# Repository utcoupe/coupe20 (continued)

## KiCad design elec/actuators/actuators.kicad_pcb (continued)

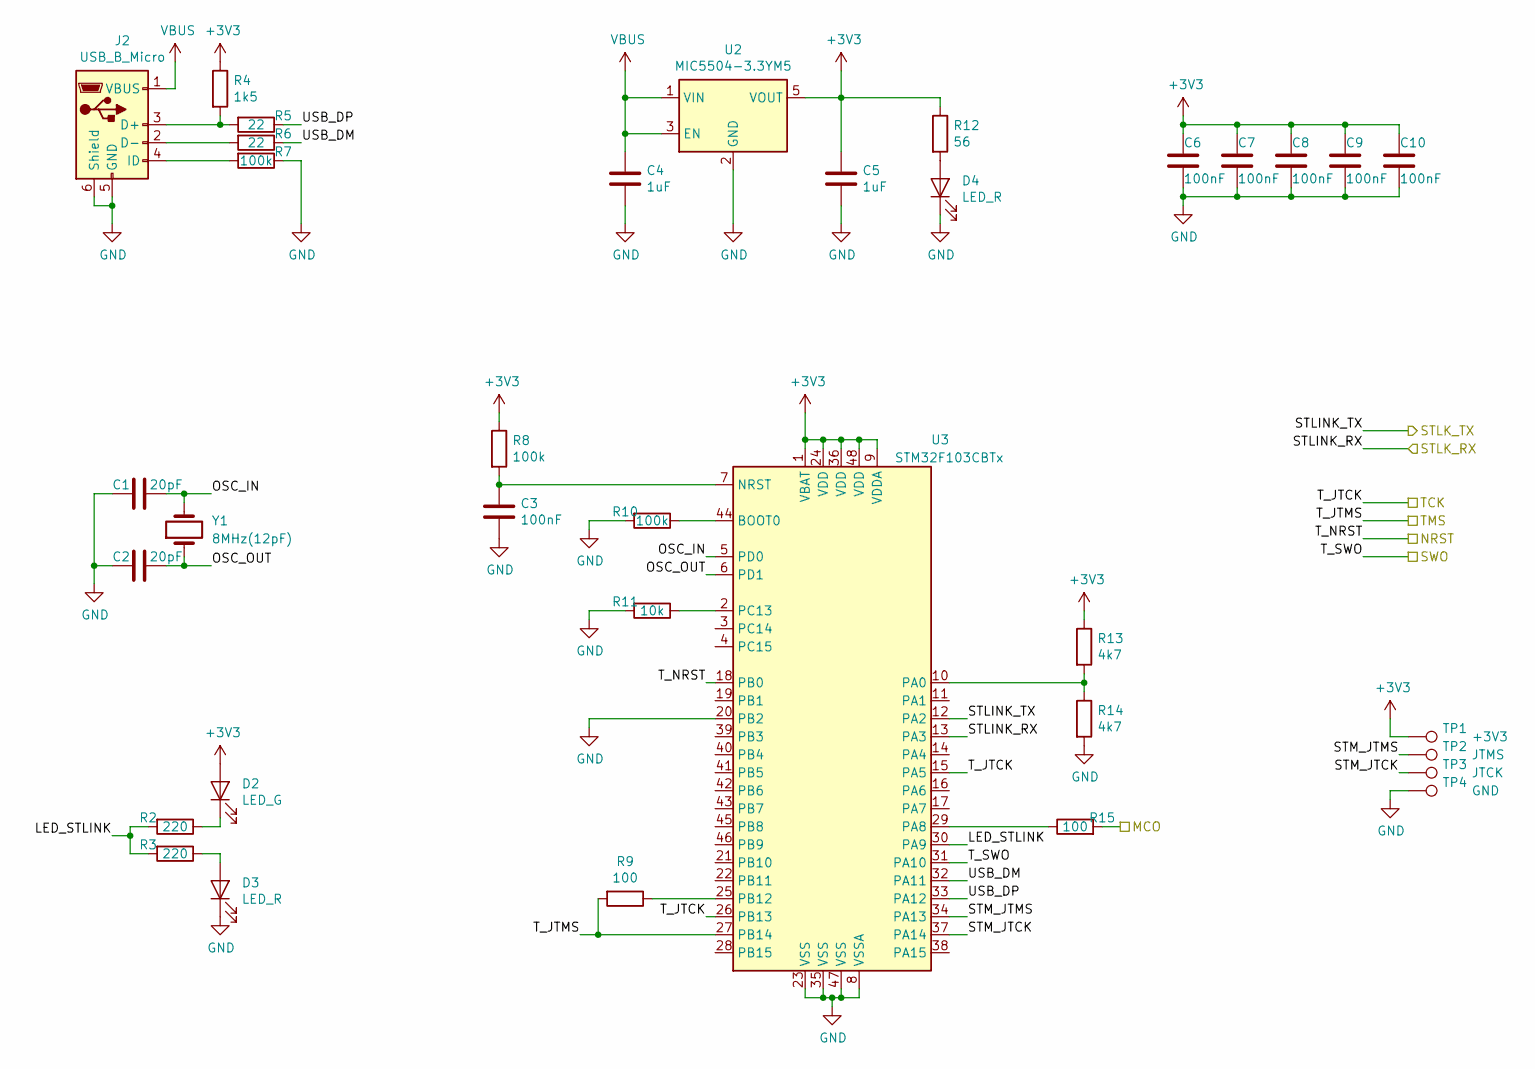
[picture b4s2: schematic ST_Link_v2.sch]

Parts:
C1, C2: 20pF; C_0805_2012Metric
C3, C6, C7, C8, C9, C10: 100nF; C_0805_2012Metric
C4, C5: 1uF; C_0805_2012Metric
D2: LED_G; LED_0805_2012Metric
D3, D4: LED_R; LED_0805_2012Metric
J2: USB_B_Micro; USB_Micro-B_Molex_47346-0001
R2, R3: 220; R_0805_2012Metric
R4: 1k5; R_0805_2012Metric
R5, R6: 22; R_0805_2012Metric
R7, R8, R10: 100k; R_0805_2012Metric
R9, R15: 100; R_0805_2012Metric
R11: 10k; R_0805_2012Metric
R12: 56; R_0805_2012Metric
R13, R14: 4k7; R_0805_2012Metric
TP1: +3V3; TestPoint_Pad_1.0x1.0mm
TP2: JTMS; TestPoint_Pad_1.0x1.0mm
TP3: JTCK; TestPoint_Pad_1.0x1.0mm
TP4: GND; TestPoint_Pad_1.0x1.0mm
U2: MIC5504-3.3YM5; SOT-23-5
U3: STM32F103CBTx; LQFP-48_7x7mm_P0.5mm
Y1: 8MHz(12pF); Crystal_SMD_HC49-SD

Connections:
+3V3: C5.1, C6.1, C7.1, C8.1, C9.1, C10.1, D2.2 (A), R4.1, R8.1, R12.1, R13.1, TP1.1, U2.5 (VOUT), U3.1 (VBAT), U3.9 (VDDA), U3.24 (VDD), U3.36 (VDD), U3.48 (VDD); also elsewhere on the board
/STM32F446RE6/MCO: R15.2; also elsewhere on the board
/STM32F446RE6/NRST: U3.18 (PB0); also elsewhere on the board
/STM32F446RE6/SWO: U3.31 (PA10); also elsewhere on the board
/STM32F446RE6/TCK: U3.15 (PA5), U3.26 (PB13); also elsewhere on the board
/STM32F446RE6/TMS: R9.2, U3.27 (PB14); also elsewhere on the board
/ST_Link_v2/LED_STLINK: R2.2, R3.2, U3.30 (PA9)
/ST_Link_v2/OSC_IN: C1.1, U3.5 (PD0), Y1.2
/ST_Link_v2/OSC_OUT: C2.2, U3.6 (PD1), Y1.1
/ST_Link_v2/STLK_RX: U3.13 (PA3); also elsewhere on the board
/ST_Link_v2/STLK_TX: U3.12 (PA2); also elsewhere on the board
/ST_Link_v2/STM_JTCK: TP3.1, U3.37 (PA14); also elsewhere on the board
/ST_Link_v2/STM_JTMS: TP2.1, U3.34 (PA13); also elsewhere on the board
/ST_Link_v2/USB_DM: R6.1, U3.32 (PA11)
/ST_Link_v2/USB_DP: R5.1, U3.33 (PA12)
unnamed: C3.1, R8.2, U3.7 (NRST)
unnamed: D2.1 (K), R2.1
unnamed: D3.2 (A), R3.1
unnamed: D4.2 (A), R12.2
unnamed: J2.2 (D-), R6.2
unnamed: J2.3 (D+), R4.2, R5.2
unnamed: J2.4 (ID), R7.2
unnamed: R9.1, U3.25 (PB12)
unnamed: R10.1, U3.44 (BOOT0)
unnamed: R11.1, U3.2 (PC13)
unnamed: R13.2, R14.1, U3.10 (PA0)
unnamed: R15.1, U3.29 (PA8)
VBUS: C4.1, J2.1 (VBUS), U2.1 (VIN), U2.3 (EN)

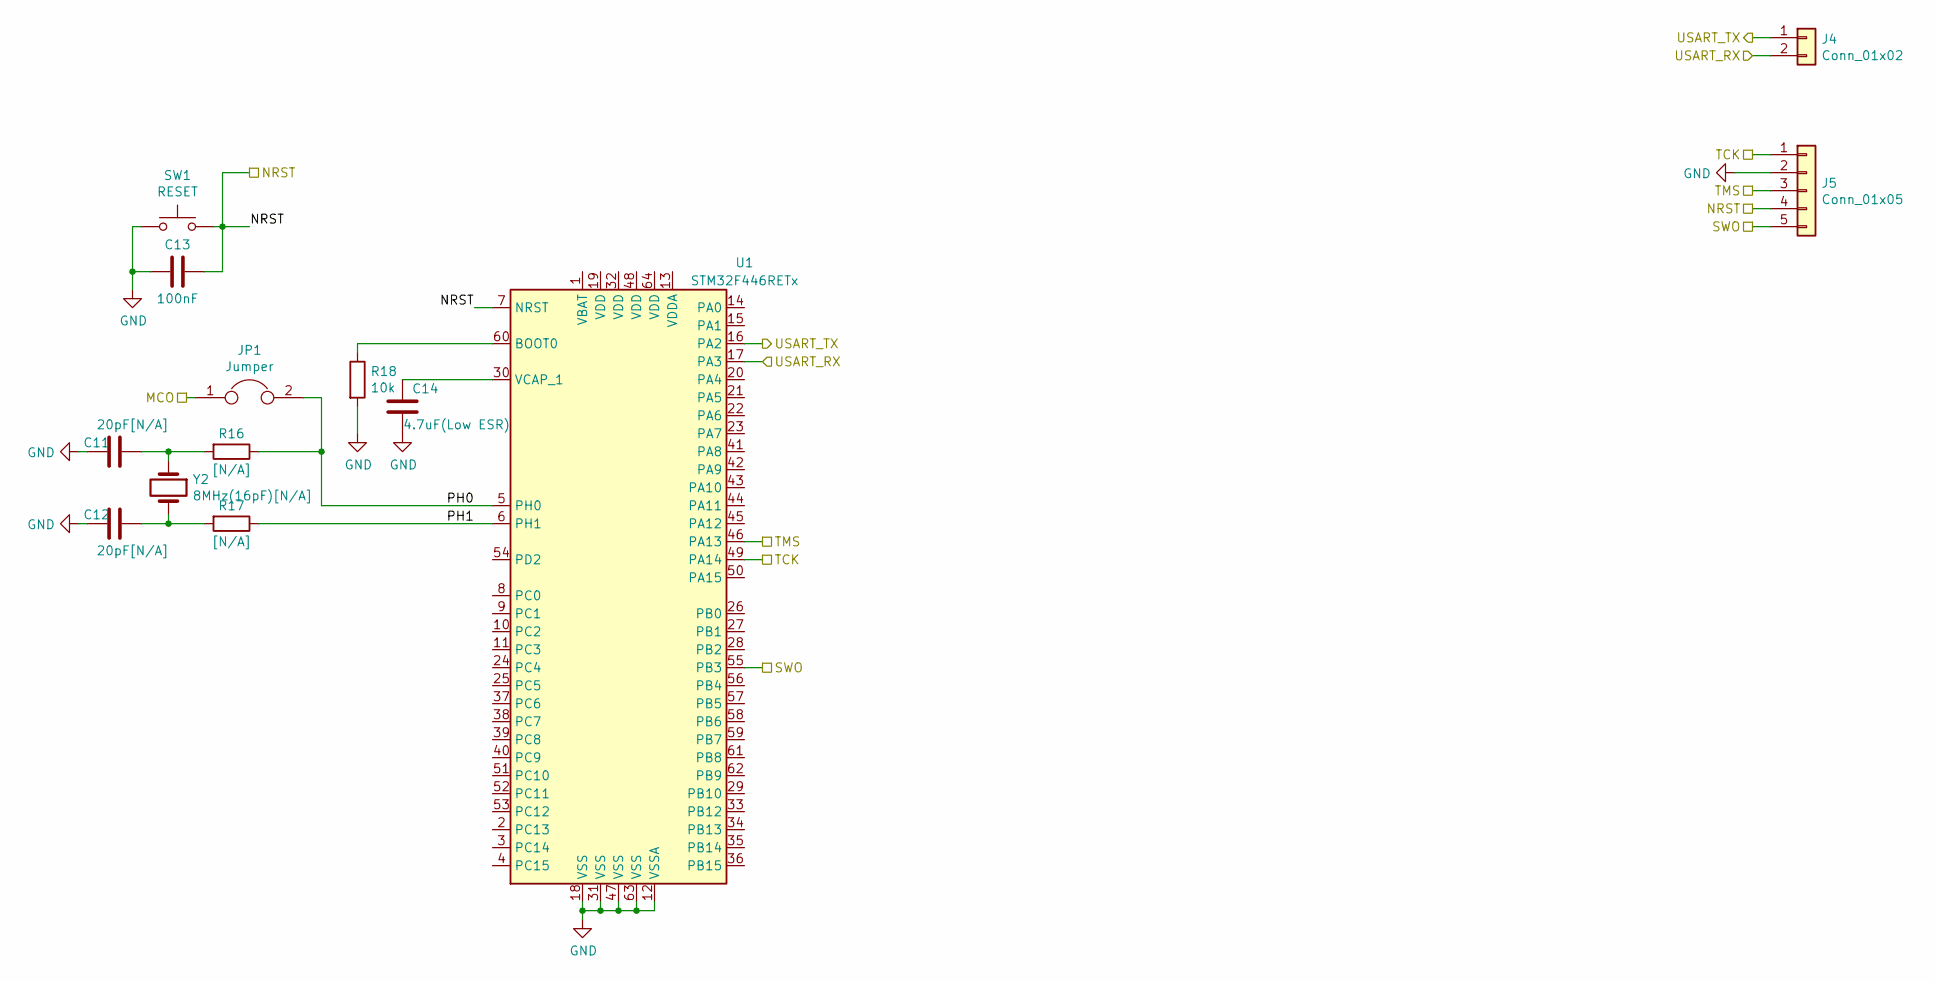
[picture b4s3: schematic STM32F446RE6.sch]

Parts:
C11, C12: 20pF[N/A]; C_0805_2012Metric
C13: 100nF; C_0805_2012Metric
C14: 4.7uF(Low ESR); C_0805_2012Metric
J4: Conn_01x02; PinHeader_1x02_P2.54mm_Vertical
J5: Conn_01x05; PinHeader_1x05_P2.54mm_Vertical
JP1: Jumper; SolderJumper-2_P1.3mm_Open_TrianglePad1.0x1.5mm
R16, R17: [N/A]; R_0805_2012Metric
R18: 10k; R_0805_2012Metric
SW1: RESET; SW_Push_1P1T_NO_CK_KSC6xxJ
U1: STM32F446RETx; LQFP-64_10x10mm_P0.5mm
Y2: 8MHz(16pF)[N/A]; Crystal_SMD_HC49-SD

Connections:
/STM32F446RE6/MCO: JP1.1; also elsewhere on the board
/STM32F446RE6/NRST: C13.1, J5.4, SW1.2, U1.7 (NRST); also elsewhere on the board
/STM32F446RE6/PH0: JP1.2, R16.1, U1.5 (PH0)
/STM32F446RE6/PH1: R17.1, U1.6 (PH1)
/STM32F446RE6/SWO: J5.5, U1.55 (PB3); also elsewhere on the board
/STM32F446RE6/TCK: J5.1, U1.49 (PA14); also elsewhere on the board
/STM32F446RE6/TMS: J5.3, U1.46 (PA13); also elsewhere on the board
/ST_Link_v2/STLK_RX: J4.1, U1.16 (PA2); also elsewhere on the board
/ST_Link_v2/STLK_TX: J4.2, U1.17 (PA3); also elsewhere on the board
unnamed: C11.1, R16.2, Y2.1
unnamed: C12.1, R17.2, Y2.2
unnamed: C14.1, U1.30 (VCAP_1)
unnamed: R18.1, U1.60 (BOOT0)

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
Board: 2 copper layers, 52 parts (0 on the bottom side), 37 nets, no tracks yet.

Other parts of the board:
J3: Conn_01x04; PinHeader_1x04_P2.54mm_Vertical

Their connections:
+3V3: J3.1; also elsewhere on the board
/ST_Link_v2/STM_JTCK: J3.3; also elsewhere on the board
/ST_Link_v2/STM_JTMS: J3.2; also elsewhere on the board

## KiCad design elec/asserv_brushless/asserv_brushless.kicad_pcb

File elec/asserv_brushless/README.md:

# Brushless PCB

[Interactive BOM](http://htmlpreview.github.io/?https://github.com/utcoupe/coupe20/blob/elec/elec/asserv_brushless/bom/ibom.html)

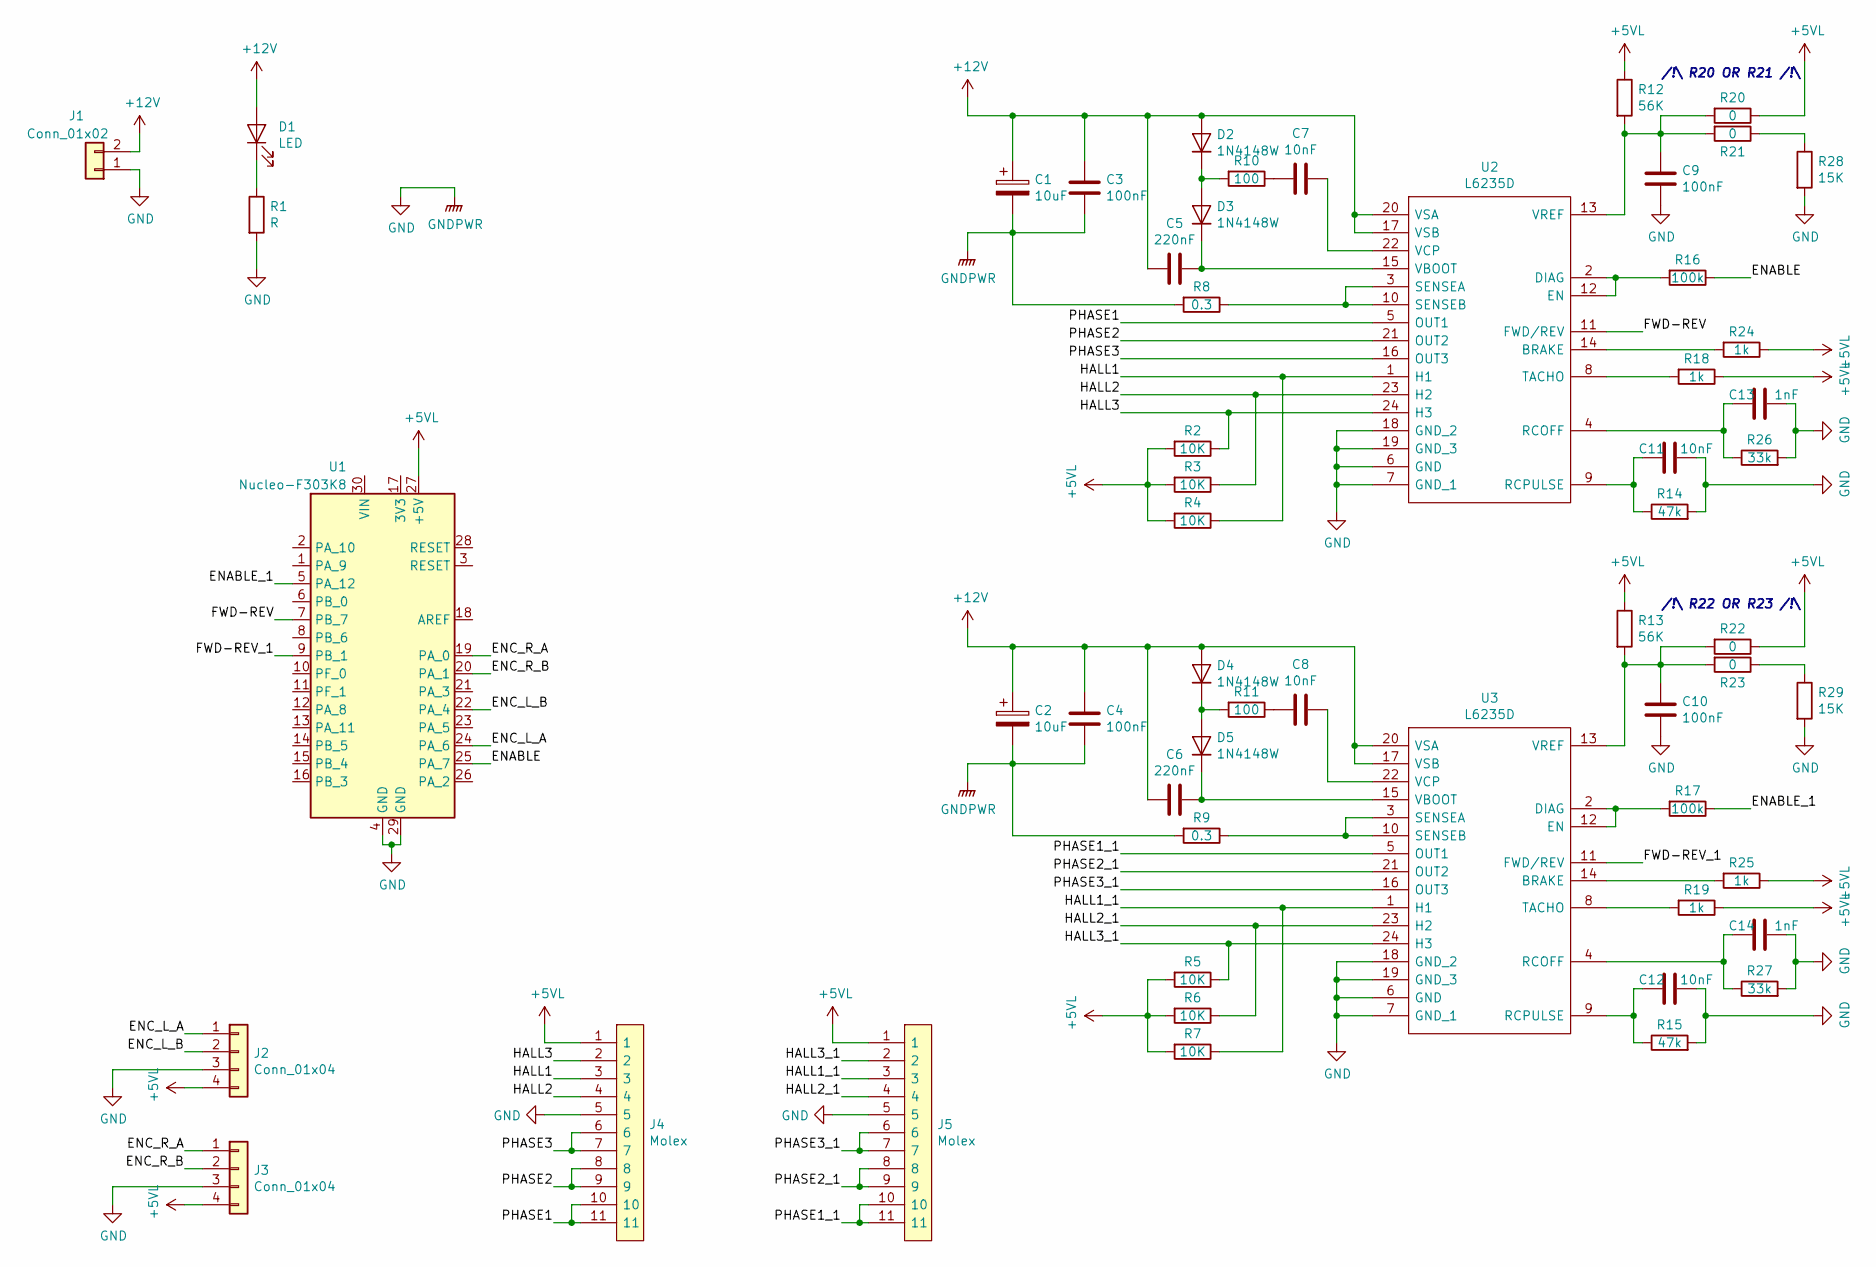
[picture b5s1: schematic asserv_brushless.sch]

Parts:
C1, C2: 10uF; CP_Elec_4x5.3
C3, C4, C9, C10: 100nF; C_0805_2012Metric
C5, C6: 220nF; C_0805_2012Metric
C7, C8, C11, C12: 10nF; C_0805_2012Metric
C13, C14: 1nF; C_0805_2012Metric
D1: LED; LED_0805_2012Metric
D2, D3, D4, D5: 1N4148W; D_SOD-123
J1: Conn_01x02; PhoenixContact_MSTBA_2,5_2-G-5,08_1x02_P5.08mm_Horizontal
J2, J3: Conn_01x04; Headers-Wire_Housings_HEADER_4POS_HE14
J4, J5: Molex; Molex_01x11_1mm_pitch_FFC-FPC; Manufacturer_Part_Number 52271-1179; Mouser Part Number 538-52271-1179
R1: R; R_0805_2012Metric
R2, R3, R4, R5, R6, R7: 10K; R_0805_2012Metric
R8, R9: 0.3; R_0805_2012Metric
R10, R11: 100; R_0805_2012Metric
R12, R13: 56K; R_0805_2012Metric
R14, R15: 47k; R_0805_2012Metric
R16, R17: 100k; R_0805_2012Metric
R18, R19, R24, R25: 1k; R_0805_2012Metric
R20, R21, R22, R23: 0; R_0805_2012Metric
R26, R27: 33k; R_0805_2012Metric
R28, R29: 15K; R_0805_2012Metric
U1: Nucleo-F303K8; NUCLEO-F303K8
U2, U3: L6235D; Manufacturer_Part_Number L6235D; Mouser Part Number 511-L6235D

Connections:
+5VL: J2.4, J3.4, J4.1, J5.1, R2.2, R3.2, R4.2, R5.2, R6.2, R7.2, R12.1, R13.1, R18.1, R19.1, R20.1, R22.1, R24.1, R25.1, U1.27 (+5V)
+12V: C1.1, C2.1, C3.1, C4.1, C5.2, C6.2, D1.2 (A), D2.2 (A), D4.2 (A), J1.2, U2.17 (VSB), U2.20 (VSA), U3.17 (VSB), U3.20 (VSA)
/ENABLE: R16.1, U1.25 (PA_7)
/ENABLE_1: R17.1, U1.5 (PA_12)
/ENC_L_A: J2.1, U1.24 (PA_6)
/ENC_L_B: J2.2, U1.22 (PA_4)
/ENC_R_A: J3.1, U1.19 (PA_0)
/ENC_R_B: J3.2, U1.20 (PA_1)
/FWD-REV: U1.7 (PB_7), U2.11 (FWD/REV)
/FWD-REV_1: U1.9 (PB_1), U3.11 (FWD/REV)
/HALL1: J4.3, R4.1, U2.1 (H1)
/HALL1_1: J5.3, R7.1, U3.1 (H1)
/HALL2: J4.4, R3.1, U2.23 (H2)
/HALL2_1: J5.4, R6.1, U3.23 (H2)
/HALL3: J4.2, R2.1, U2.24 (H3)
/HALL3_1: J5.2, R5.1, U3.24 (H3)
/PHASE1: J4.10, J4.11, U2.5 (OUT1)
/PHASE1_1: J5.10, J5.11, U3.5 (OUT1)
/PHASE2: J4.8, J4.9, U2.21 (OUT2)
/PHASE2_1: J5.8, J5.9, U3.21 (OUT2)
/PHASE3: J4.6, J4.7, U2.16 (OUT3)
/PHASE3_1: J5.6, J5.7, U3.16 (OUT3)
GND: C1.2, C2.2, C3.2, C4.2, C9.2, C10.2, C11.1, C12.1, C13.1, C14.1, J1.1, J2.3, J3.3, J4.5, J5.5, R1.2, R8.2, R9.2, R14.2, R15.2, R26.2, R27.2, R28.2, R29.2, U1.4 (GND), U1.29 (GND), U2.6 (GND), U2.7 (GND_1), U2.18 (GND_2), U2.19 (GND_3), U3.6 (GND), U3.7 (GND_1), U3.18 (GND_2), U3.19 (GND_3)
unnamed: C5.1, D3.1 (K), U2.15 (VBOOT)
unnamed: C6.1, D5.1 (K), U3.15 (VBOOT)
unnamed: C7.1, U2.22 (VCP)
unnamed: C7.2, R10.1
unnamed: C8.1, U3.22 (VCP)
unnamed: C8.2, R11.1
unnamed: C9.1, R12.2, R20.2, R21.2, U2.13 (VREF)
unnamed: C10.1, R13.2, R22.2, R23.2, U3.13 (VREF)
unnamed: C11.2, R14.1, U2.9 (RCPULSE)
unnamed: C12.2, R15.1, U3.9 (RCPULSE)
unnamed: C13.2, R26.1, U2.4 (RCOFF)
unnamed: C14.2, R27.1, U3.4 (RCOFF)
unnamed: D1.1 (K), R1.1
unnamed: D2.1 (K), D3.2 (A), R10.2
unnamed: D4.1 (K), D5.2 (A), R11.2
unnamed: R8.1, U2.3 (SENSEA), U2.10 (SENSEB)
unnamed: R9.1, U3.3 (SENSEA), U3.10 (SENSEB)
unnamed: R16.2, U2.2 (DIAG), U2.12 (EN)
unnamed: R17.2, U3.2 (DIAG), U3.12 (EN)
unnamed: R18.2, U2.8 (TACHO)
unnamed: R19.2, U3.8 (TACHO)
unnamed: R21.1, R28.1
unnamed: R23.1, R29.1
unnamed: R24.2, U2.14 (BRAKE)
unnamed: R25.2, U3.14 (BRAKE)

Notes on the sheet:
/!\ R20 OR R21 /!\
/!\ R22 OR R23 /!\

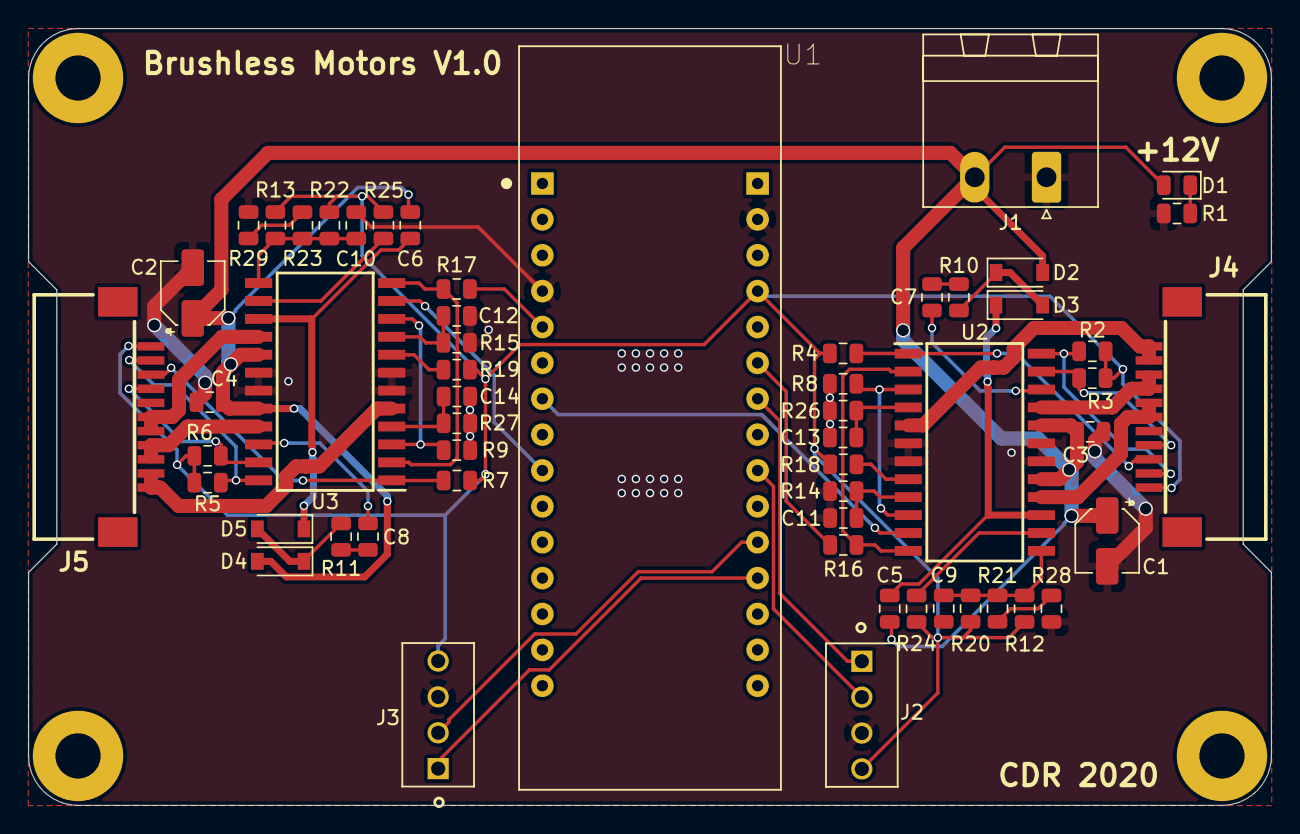
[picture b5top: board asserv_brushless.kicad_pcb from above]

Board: 2 copper layers, 88.0 x 55.0 mm, 56 parts (0 on the bottom side), 48 nets.

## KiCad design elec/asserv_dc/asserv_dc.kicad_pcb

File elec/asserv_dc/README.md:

# DC motors PCB

[Interactive BOM](http://htmlpreview.github.io/?https://github.com/utcoupe/coupe20/blob/elec/elec/asserv_dc/bom/ibom.html)

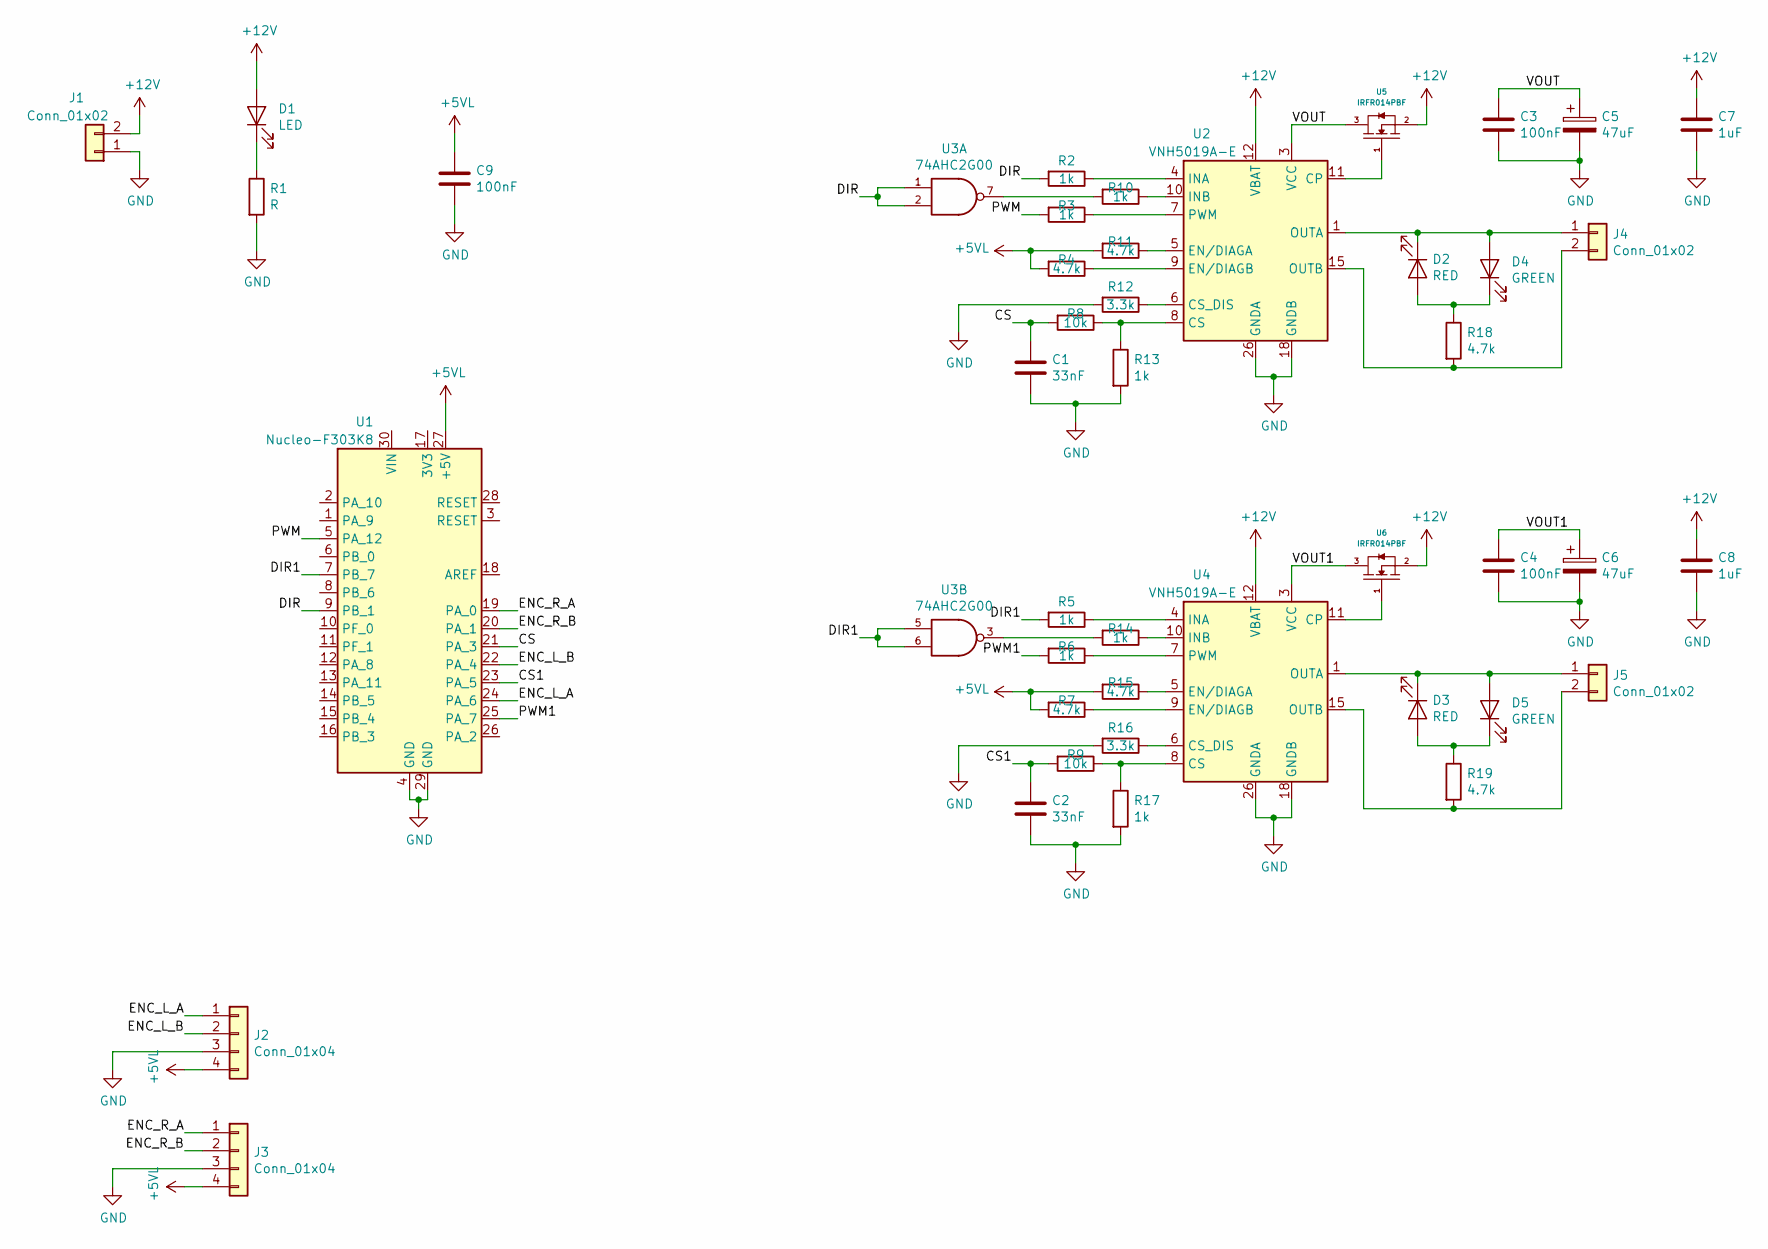
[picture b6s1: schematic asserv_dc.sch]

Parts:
C1, C2: 33nF; C_0805_2012Metric
C3, C4, C9: 100nF; C_0805_2012Metric
C5, C6: 47uF; CP_Elec_4x5.3
C7, C8: 1uF; C_0805_2012Metric
D1: LED; LED_0805_2012Metric
D2, D3: RED; LED_0805_2012Metric
D4, D5: GREEN; LED_0805_2012Metric
J1: Conn_01x02; PhoenixContact_MSTBA_2,5_2-G-5,08_1x02_P5.08mm_Horizontal
J2, J3: Conn_01x04; Headers-Wire_Housings_HEADER_4POS_HE14
J4, J5: Conn_01x02; PhoenixContact_MC_1,5_2-G-3.5_1x02_P3.50mm_Horizontal
R1: R; R_0805_2012Metric
R2, R3, R5, R6, R10, R13, R14, R17: 1k; R_0805_2012Metric
R4, R7, R11, R15, R18, R19: 4.7k; R_0805_2012Metric
R8, R9: 10k; R_0805_2012Metric
R12, R16: 3.3k; R_0805_2012Metric
U1: Nucleo-F303K8; NUCLEO-F303K8
U2, U4: VNH5019A-E; ST_MultiPowerSO-30
U3: 74AHC2G00; TSSOP-8_3x3mm_P0.65mm
U5, U6: IRFR014PBF

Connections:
+5VL: C9.1, J2.4, J3.4, R4.2, R7.2, R11.2, R15.2, U1.27 (+5V)
+12V: C7.1, C8.1, D1.2 (A), J1.2, U2.12 (VBAT), U4.12 (VBAT), U5.2, U6.2
/CS: C1.1, R8.2, U1.21 (PA_3)
/CS1: C2.1, R9.2, U1.23 (PA_5)
/DIR: R2.2, U1.9 (PB_1), U3.1, U3.2
/DIR1: R5.2, U1.7 (PB_7), U3.5, U3.6
/ENC_L_A: J2.1, U1.24 (PA_6)
/ENC_L_B: J2.2, U1.22 (PA_4)
/ENC_R_A: J3.1, U1.19 (PA_0)
/ENC_R_B: J3.2, U1.20 (PA_1)
/PWM: R3.2, U1.5 (PA_12)
/PWM1: R6.2, U1.25 (PA_7)
/VOUT: C3.1, C5.1, U2.3 (VCC), U2.13 (VCC), U2.23 (VCC), U2.31 (VCC), U5.3
/VOUT1: C4.1, C6.1, U4.3 (VCC), U4.13 (VCC), U4.23 (VCC), U4.31 (VCC), U6.3
GND: C1.2, C2.2, C3.2, C4.2, C5.2, C6.2, C7.2, C8.2, C9.2, J1.1, J2.3, J3.3, R1.2, R12.2, R13.2, R16.2, R17.2, U1.4 (GND), U1.29 (GND), U2.18 (GNDB), U2.19 (GNDB), U2.20 (GNDB), U2.26 (GNDA), U2.27 (GNDA), U2.28 (GNDA), U3.4 (GND), U4.18 (GNDB), U4.19 (GNDB), U4.20 (GNDB), U4.26 (GNDA), U4.27 (GNDA), U4.28 (GNDA)
unnamed: D1.1 (K), R1.1
unnamed: D2.1 (K), D4.2 (A), J4.1, U2.1 (OUTA), U2.25 (OUTA), U2.30 (OUTA), U2.33 (OUTA)
unnamed: D2.2 (A), D4.1 (K), R18.1
unnamed: D3.1 (K), D5.2 (A), J5.1, U4.1 (OUTA), U4.25 (OUTA), U4.30 (OUTA), U4.33 (OUTA)
unnamed: D3.2 (A), D5.1 (K), R19.1
unnamed: J4.2, R18.2, U2.15 (OUTB), U2.16 (OUTB), U2.21 (OUTB), U2.32 (OUTB)
unnamed: J5.2, R19.2, U4.15 (OUTB), U4.16 (OUTB), U4.21 (OUTB), U4.32 (OUTB)
unnamed: R2.1, U2.4 (INA)
unnamed: R3.1, U2.7 (PWM)
unnamed: R4.1, U2.9 (EN/DIAGB)
unnamed: R5.1, U4.4 (INA)
unnamed: R6.1, U4.7 (PWM)
unnamed: R7.1, U4.9 (EN/DIAGB)
unnamed: R10.1, U2.10 (INB)
unnamed: R10.2, U3.7
unnamed: R11.1, U2.5 (EN/DIAGA)
unnamed: R12.1, U2.6 (CS_DIS)
unnamed: R8.1, R13.1, U2.8 (CS)
unnamed: R14.1, U4.10 (INB)
unnamed: R14.2, U3.3
unnamed: R15.1, U4.5 (EN/DIAGA)
unnamed: R16.1, U4.6 (CS_DIS)
unnamed: R9.1, R17.1, U4.8 (CS)
unnamed: U2.11 (CP), U5.1
unnamed: U4.11 (CP), U6.1
VCC: U3.8 (VCC)

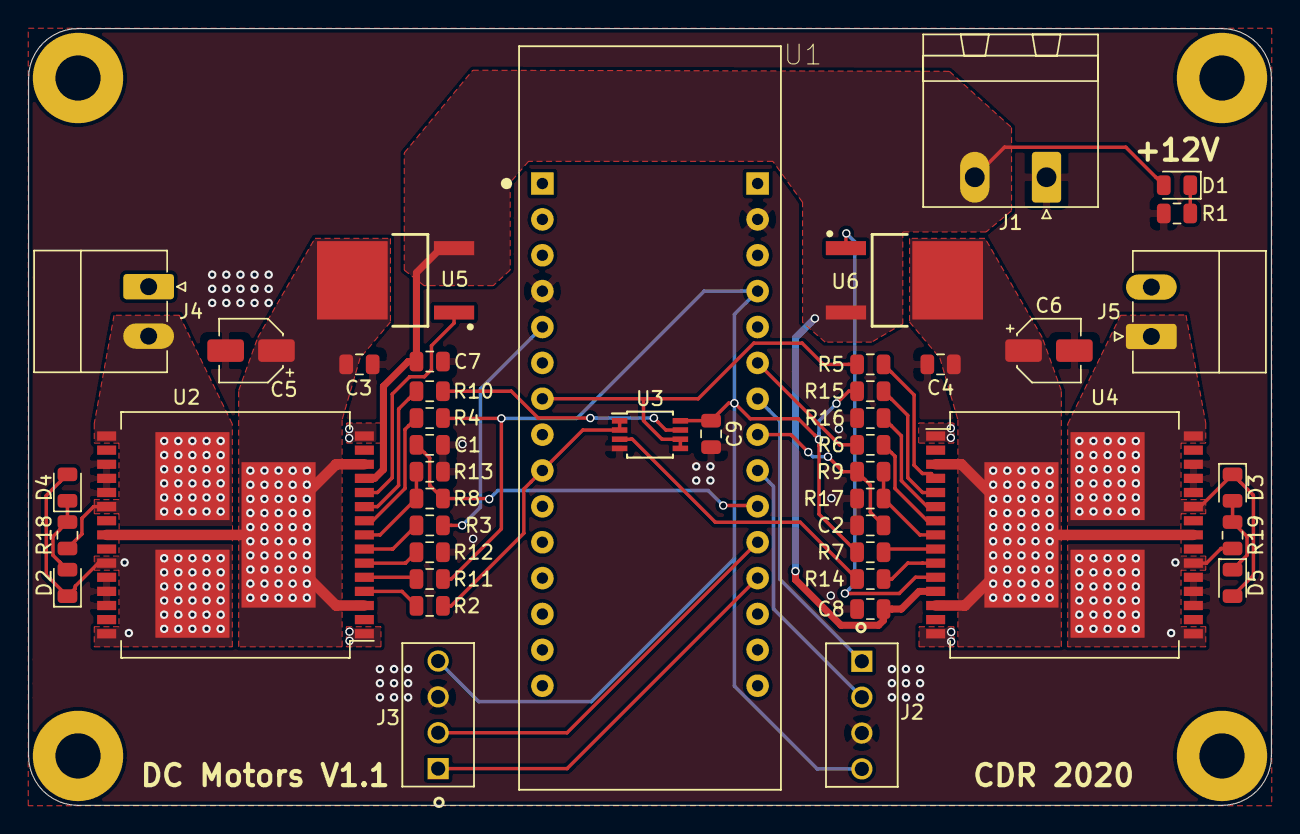
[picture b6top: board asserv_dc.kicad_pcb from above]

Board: 2 copper layers, 88.0 x 55.0 mm, 44 parts (0 on the bottom side), 40 nets.

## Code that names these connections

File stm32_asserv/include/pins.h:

#ifndef PINS_H
#define PINS_H

#include "stm32f3xx_hal_def.h"
#include "stm32f3xx_hal.h"

// ***************************************************
// * WARNING: THESE PINS ARE DEFINED FOR STM32F303K8 *
// ***************************************************

// **************** ENCODERS *****************
// Right encoder, signal A: PA_6 (A6)
#define ENC_R_A_Pin GPIO_PIN_6
#define ENC_R_A_GPIO_Port GPIOA

// Right encoder, signal B: PA_4 (A4)
#define ENC_R_B_Pin GPIO_PIN_4
#define ENC_R_B_GPIO_Port GPIOA

// Left encoder, signal A: PA_0 (A0)
#define ENC_L_A_Pin GPIO_PIN_0
#define ENC_L_A_GPIO_Port GPIOA

// Left encoder, signal B: PA_1 (A1)
#define ENC_L_B_Pin GPIO_PIN_1
#define ENC_L_B_GPIO_Port GPIOA

// ******************* MOTORS *****************

// Left motor, PWM control: PA_12 (D2)
#define MOT_L_EN_Pin GPIO_PIN_12
#define MOT_L_EN_GPIO_Port GPIOA

// Left motor, direction of rotation: PB_1 (D6)
#define MOT_L_DIR_Pin GPIO_PIN_1
#define MOT_L_DIR_GPIO_Port GPIOB

// Right motor, PWM control: PA_7 (A7)
#define MOT_R_EN_Pin GPIO_PIN_7
#define MOT_R_EN_GPIO_Port GPIOA

// Right motor, direction of rotation: PB_7 (D4)
#define MOT_R_DIR_Pin GPIO_PIN_7
#define MOT_R_DIR_GPIO_Port GPIOB

// ******************* OTHERS *******************

// Built-in LED3: PB_3 (D13), SHOULD NOT BE CONNECTED TO ANYTHING ELSE
#define TEST_LED_Pin GPIO_PIN_3
#define TEST_LED_GPIO_Port GPIOB

#define HIGH 	GPIO_PIN_SET
#define LOW 	GPIO_PIN_RESET

#define L_ENC_TIM TIM2
#define R_ENC_TIM TIM3

#endif

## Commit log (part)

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2019-03-09 :bug: Fixed wrong directory
2019-03-09 Fix install script error msg when launched from the wrong dir
    + typo
2019-03-09 :bug: Fixed map crash
2019-03-10 modification des msg
2019-03-10 :sparkles: Added geometry_msgs::Pose2D converters
2019-03-10 messages arduino
2019-03-10 :wrench: Adapted code
2019-03-11 :wrench: Cleaned a bit
2019-03-11 :bug: Forgotten file :scream:
2019-03-14 Fixed error when navigator is told to disable pathfinder
    Navigation failed: local variable 'path' referenced before assignment
2019-03-14 Fixed automatic direction in navigator goto
2019-03-21 variables pour le bras
2019-03-21 Fixed navigator bug when asking to disable pathfinder
2019-03-21 :bug: Fixed pathfinder not working
2019-03-21 Created map waypoints, started GR strategy
2019-03-21 :recycle: Removed useless can init
2019-03-22 :wrench: Parameter packs are awesome to simplify code!
2019-03-22 oopsie, removing debug
2019-03-22 Solved auto_stop asservi simu angle bug
2019-03-23 :wrench: Cleaning code
2019-03-23 :sparkles: Added OccupancyGrid + :bug: Fixed very old bug
2019-03-23 When GOTOA, navigator minimizes the end rotation
2019-03-23 Interactive markers GOTO + GOTOA (with pathfinder disabled)
2019-03-23 Pathfinder enabled on interactive markers
2019-03-30 Started adapting gr strategy
2019-03-30 Fixed static_map team swap
2019-03-30 :wrench: Started to adapt code
2019-03-30 :wrench: Pathfinder now using new occupancy system
2019-03-30 test unitaire sur stepper
2019-04-03 messages AX12
2019-04-04 Added map_transfer to scheduler (removed spawn atoms in GR map)
2019-04-04 Ax12 subscribes to topic for joint commands only
    [Not Tested]
    topic : drivers/ax12/simple_command
2019-04-06 ax12 msg
2019-04-06 Switch to 2 constructors
2019-04-06 Map GetTerrain changed to GetContext (robot shape) + Adapted asserv_simu
2019-04-06 Command topic handles wheel mode + cleaned code
2019-04-06 :bug: Fixed service name
2019-04-06 game manager sleep(5)
2019-04-11 :bug: Fixed potential crash with multithreading
2019-04-11 :sparkles: Pathfinder starting with auto margin
2019-04-11 Revert ":bug: Fixed C++17 atomic init with gcc5" since this is not the issue
    This reverts commit d8d47193a4e69ae47c69922fd7c8a1673f03bead.
2019-04-11 :bug: Added cpp header <atomic>
2019-04-15 :wrench: General performance improvements --- MAP NOT WORKING
2019-04-22 :bug: Fiwed pathfinder not initializing its map + added logs + fiwed typos
2019-04-24 :books: Added documentation to Obstacle
2019-04-24 :books: Documented Collision class
2019-04-25 :wrench: ObstacleVelocity is unique, not shared
2019-04-26 first
2019-04-26 Code door arduino et stepper
2019-04-26 create pkg ard_gr_front
2019-04-26 AX12 message
2019-04-29 :wrench: Inverted relation between robot and asserv tf
2019-04-29 :wrench: Localizer now publishing on asserv tf
2019-04-29 :wrench: Asserv now using tf
2019-04-29 :wrench: Navigator now using tf
2019-05-01 :wrench: Updated msg
2019-05-01 :wrench: Addapted navigator to new CollisionLevel system
2019-05-02 Created `sensors` arduino (without actuators), will go in the LattePanda
2019-05-03 modif sur la structure du robot => refonte soft
2019-05-04 Update pkg names & make actioneurs code compile
2019-05-04 rename for cconformity. Ros messages work
2019-05-04 Add rest of msg #TODO functions triggered
2019-05-05 :wrench: Collisions now retrieving robot shpae + added more doc
2019-05-05 :wrench: General performance improvements
2019-05-07 :wrench: Unit tests are compiled only on master and devel
2019-05-07 :bug: Fixed bash syntax
2019-05-07 :bug: More logs
2019-05-07 :bug: Tests compiled ?
2019-05-07 :bug: Boolean is maybe quantum...
2019-05-07 :bug: I realy need to sleep...
2019-05-09 :sparkles: Fixed cmake var + added some tests as demo
2019-05-09 :wrench: Added more unit tests
2019-05-11 remove back door & fill stepper functions
2019-05-11 modification code pour stepper
2019-05-11 :books: Added documentation for STM32 pins
2019-05-11 PR now loads goldenium in strategy + bug fixes
2019-05-13 :wrench: Removed macros as functions.
2019-05-13 :ledger: Forgot to clean code
2019-05-13 :wrench: Reset obstacles at each run
2019-05-13 Hardcoded goldenium waypoint for right side ¯\_(ツ)_/¯
2019-05-13 oops wrong pos
2019-05-16 Added publisher function (not tested yet)
2019-05-16 Theorical code done #TODO calibrate constants
2019-05-16 test unit sur différentes actions
2019-05-16 adaptation du code principal
2019-05-17 msg tower modify
2019-05-17 unit test
2019-05-18 :wrench: Switched to coupe18 PR asserv parameters
2019-05-24 :bug: Fixed typo
2019-05-24 :twisted_rightwards_arrows: Random changes to maybe fix asserv bugs
2019-05-24 :bug: Fixed double promotion
2019-05-24 Cleanup & adapt code. Just needs testing on saturday night
2019-05-25 fixed lidar publisher
2019-05-25 Security on events when game off
2019-05-25 PR code
2019-05-26 code working (except tower but it worked right before so issue should not be in code) #TODO calibrate stepper & publisher
2019-05-26 comment out debugging nh.loginfo
2019-05-26 Add Scale door time security & camion poubelle to dump pucks #todo calibrate pucks sort time & tighten GAME_OFF security
2019-05-27 listen to ROS msgs while doing action blocks
2019-05-27 change msg for conformity & delete useless pkg
2019-05-27 added switch for pucks door
2019-05-27 ai fixes
2019-05-27 HMI qui fonctionne
2019-05-28 hmi code
2019-05-28 HMI ok avec jack mais que droite TODO : gauche
2019-05-28 Adapted pr asserv to blackBrushless
2019-05-28 Added delay to jack in pr strat + include fix
2019-05-28 Added homologations pr strats
2019-05-29 Adapted pr strat
2019-05-30 :wrench: Belt pins for latte leonardo
2019-05-30 :wrench: Added latte leonardo
2019-05-30 portfinder try multiple times to open STM32
2019-07-18 :books: Added more documentation + :bug: Fixed some potential bugs.
2019-08-23 :bug: Fixed wrong GPG key
2019-09-02 :bug: Fixed command not recognized
2019-09-14 Fix urg_node not starting (python indent typo)
2019-11-02 Update install_utcoupe_setup
2019-11-02 Replace 'coupe19' with 'coupe20'
2019-11-02 Update travis
2019-11-02 Changed some coupe18 to coupe20
2019-11-08 Fix comment
2019-11-08 Add wheelbase in robot xml
2019-11-08 Add wheelbase for pr
2019-11-08 Add Robot msg with added parameters like wheelbase
2019-11-08 Add curve service for webclient
2019-11-20 tf frames: robot -> robot_front and assert -> robot
2019-11-27 POC curve control
2019-11-27 greater error for asserv simu for testing
2019-11-30 PCBs 2020 :open_mouth:
2019-12-01 updated map for coupe20
2019-12-01 WIP : control for following Bezier curves
2019-12-01 Add author
2019-12-04 Fix include
2019-12-06 simplify command law
2019-12-06 Add points to Bezier curve
2019-12-07 Refactor & change some parameters
2019-12-07 refactor: remove brushlessMotor.cpp
2019-12-07 refactor: naming convention
2019-12-07 uggly => ugly
2019-12-07 changing cut out
2019-12-07 fix pwm and speed services
2019-12-07 fetch protocol from stm32_asserv
2019-12-07 fix bug uint32_to_int16
2019-12-07 update pins
2019-12-07 invert motor timers
2019-12-08 Replace uint32_to_int16 by cast
2019-12-09 Remove tan approximation - stm32 has more power
2019-12-10 More accessibility to fifo goals
2019-12-10 Pathfinder sends less goals
2019-12-10 add auto_stop in PWM
2019-12-10 add auto_stop timer
2019-12-10 Changed parameters
2019-12-10 Update control law
2019-12-10 static_cast fix
2019-12-11 Added saturation angle. Control suited for both straight and curve paths.
2019-12-14 Increase serial buffer size
2019-12-14 Clear all goals when blocked instead of only next
2019-12-22 Add shared library to run in python
2019-12-22 More explicit names
2019-12-22 Clean files & add comment
2019-12-23 Fix : duplicate fabsf
2019-12-23 Fix dependencies for lib
2019-12-23 completely decorrelate control from stm32 functions & remove useless stuff
2019-12-23 Decorrelate protocol logic from serial
2019-12-23 Simulate protocol.cpp in simu
2019-12-23 fix: old file name
2019-12-24 Rm useless functions
2019-12-26 Add pause bit to simu
2019-12-26 add non stm32-specific init functions
2019-12-26 Add position tracking from inside stm32lib
2019-12-26 bugfix: goal reached detection
2019-12-26 Fix backwards = 0 instead of -1 in stm32 asserv
2019-12-26 bugfix: 2 digit-id not parsed
2019-12-26 change some parameters
2019-12-26 Add GET_X orders
2019-12-26 update robot raw position in simu
2019-12-26 Fix id correspondance between asserv_real and ard_asserv_node
2019-12-26 remove arduino asserv
2019-12-26 Add setCurrentGoalReached function
2019-12-27 Implement border logic and auto_stop
2019-12-27 bugfixes auto_stop
2019-12-27 :recycle: Removed custom startup asm
2019-12-27 refactor: name separation between shared files and stm32 only
2019-12-27 Added first set of unit tests
2019-12-27 small addition to test instructions
2019-12-28 add test for goto #TODO add more test cases
2019-12-28 add gitignore for .pyc from script files
2019-12-28 :wrench: Switch to newlib-nano + re-enabling exceptions + removed unused files
2019-12-28 :wrench: Suppressed unused var warnings
2019-12-28 :wrench: Removed useless CMake directives
2020-01-12 lib update
2020-01-12 USB hub Power dispatch V1
2020-01-15 ESD protection on data lines
2020-01-15 update img
2020-01-16 .gitignore and .gitattributes
2020-01-25 fix: get right angle from coders
2020-01-25 add doc
2020-01-30 update Kicad lib
2020-01-30 fix : wheel spd formula
2020-02-17 add comment
2020-02-18 2020 rules
2020-02-19 fix remove segments inside circles
2020-02-19 fix index out of scope
2020-02-19 fix equation mistake
2020-02-19 update params
2020-02-24 add constant for nb of points in bezier curve
2020-02-28 :wrench: Use C++ new/delete instead of C malloc/free
2020-02-29 Fix schematic
2020-02-29 :wrench: Removed useless files + fix dependency
2020-02-29 :bug: Maybe fixed Eigen version in kinetic
2020-03-01 Added doc for gdb + shortcut
2020-03-01 Use alias for gdb
2020-03-02 V2.0 : fix dumb mistakes (capacitors pin 25 and 62, lower capacitance ESD diodes, RESET_N R-C, CFG_SEL2 and VBUS_DET resistor divider)
2020-03-03 add a message confirming the simu build passed
2020-03-04 Remove useless type ctlSpeed
2020-03-04 Update how the splines affect the command && add TODO
2020-03-06 Use less points for interpolation
2020-03-06 V1.1 : fix current sense (CS and CS1) pins of VNH5019 not connected to uC
2020-03-06 Add A4988 step file
2020-03-08 Add ST-Link/v2 schematic
2020-03-09 Add function wrapToPI to get an angle between 0 and Pi
2020-03-09 Use first working version of the interpolation
    The current program seems to be working for any path. It should be noted that the
    number of points was reduced in order to avoid the algorithm from getting overcrowded
2020-03-09 Better tuning
2020-03-09 Refine tuning for the interpolation, use of abs value of da_next and rework of wrapToPI
2020-03-10 warn user when asserv_simu lib is missing
2020-03-11 Change enemy test robot shape to circle
2020-03-12 Switched raw ptr to reference_wrapper on Obstacle
2020-03-16 Add rosbag lidar data
2020-03-16 Disable position feedback from ssimu (temporary measure to work with rosbags)
2020-03-17 PCB dispatching only power in case of the USB hub not working...
2020-03-17 Rename project files
2020-03-19 Add routed PCB without GNDs and update µC sch
2020-03-19 GND done, silkscreen done and some minor fixes
2020-03-19 :wrench: Moved all asserv files + setup cmake (NOT TESTED)
2020-03-20 Add step file, bom, pdf schematic
2020-03-20 Fix missing vias
2020-03-21 :bug: Maybe fixed docker issue
2020-03-21 :wrench: Removed compilation flag
2020-03-21 :bug: Removed too recent gcc flags
2020-03-21 :sparkles: Added basic metric exporter
2020-03-21 :bug: Force UTF-8 encoding
2020-03-21 :bug: Fixed wrong dictionary
2020-03-22 :sparkles: Added metric sample case (python)
2020-03-22 :sparkles: Added cpp metric lib
2020-03-22 Add Nucleo stm32f446re datasheet
2020-03-23 Fix missing via
2020-03-23 Fix serial 3 and 5 reversed labels
2020-03-23 Add gerber files
2020-03-29 :bug: Fixed python submodule not installed
2020-03-29 :recycle: Tidied up CMakeLists
2020-03-31 :bug: Fixed error when packages are already installed
2020-04-03 :sparkles: Added example for chronometer metric
